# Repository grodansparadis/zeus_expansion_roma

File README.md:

<h1>Zeus Expansion Roma</h1>

433Mhz RF add on card with Zeus expansion connector. Fits the 
<a href="http://www.grodansparadis.com/odessa/odessa.html">Odessa</a> module
among other modules.

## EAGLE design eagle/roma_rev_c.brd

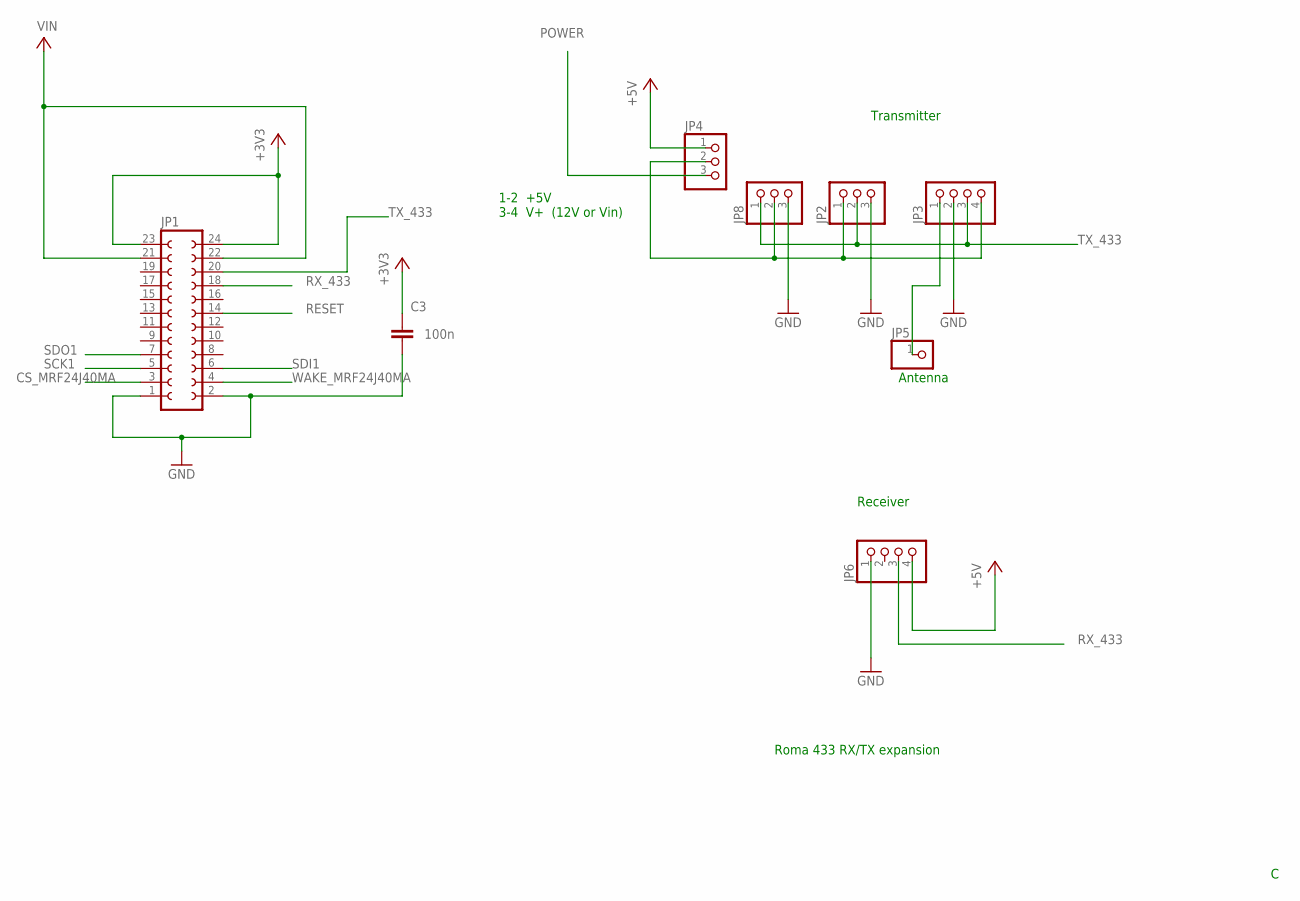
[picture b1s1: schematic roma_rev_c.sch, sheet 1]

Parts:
C3: 100n; C0805
JP1: FE12-2
JP2, JP4, JP8: PINHD-1X3; 1X03
JP3, JP6: PINHD-1X4; 1X04
JP5: PINHD-1X1; 1X01

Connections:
+3V3: C3.1, JP1.23, JP1.24; also elsewhere on the board
+5V: JP4.1, JP6.4; also elsewhere on the board
CS_MRF24J40MA: JP1.3; also elsewhere on the board
GND: C3.2, JP1.1, JP1.2, JP2.3, JP3.2, JP6.1, JP8.3; also elsewhere on the board
unnamed: JP2.1, JP3.4, JP4.2, JP8.2
unnamed: JP3.1, JP5.1
POWER: JP4.3; also elsewhere on the board
RESET: JP1.14; also elsewhere on the board
RX_433: JP1.18, JP6.3; also elsewhere on the board
SCK1: JP1.5; also elsewhere on the board
SDI1: JP1.6; also elsewhere on the board
SDO1: JP1.7; also elsewhere on the board
TX_433: JP1.20, JP2.2, JP3.3, JP8.1
VIN: JP1.21, JP1.22; also elsewhere on the board
WAKE_MRF24J40MA: JP1.4; also elsewhere on the board

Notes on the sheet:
Roma 433 RX/TX expansion
Transmitter
Antenna
Receiver
1-2 +5V 3-4 V+ (12V or Vin)

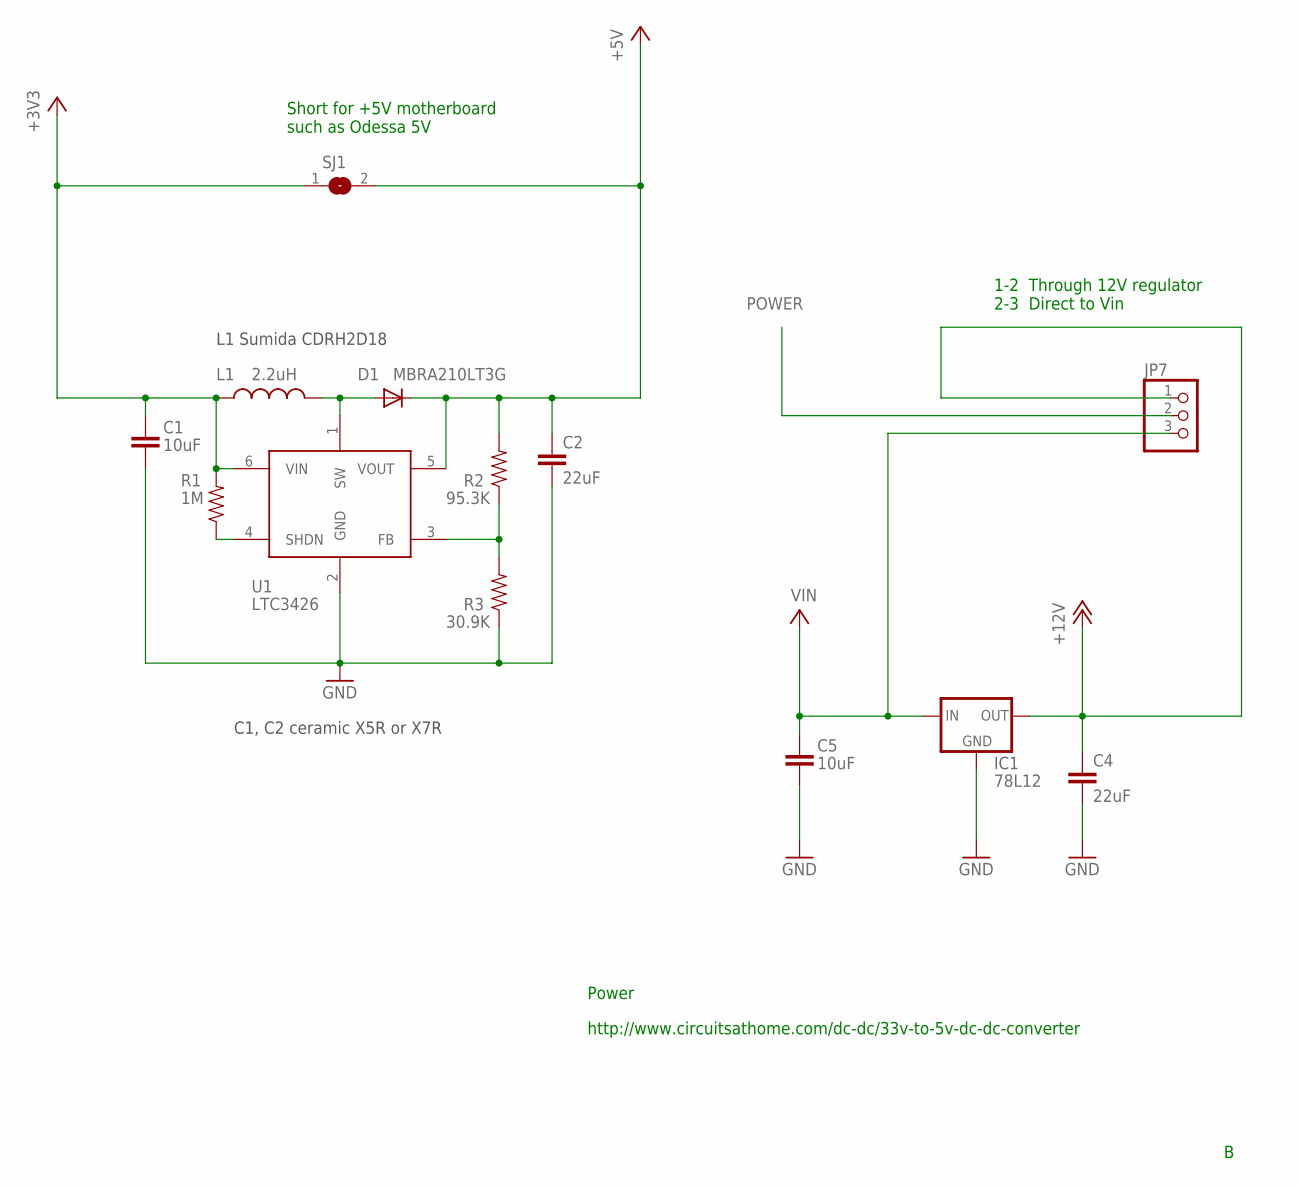
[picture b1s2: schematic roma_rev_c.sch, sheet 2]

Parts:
C1, C5: 10uF; 1210
C2, C4: 22uF; 1210
D1: MBRA210LT3G; SMA-DIODE
IC1: 78L12; 78LXX
JP7: PINHD-1X3; 1X03
L1: 2.2uH; 1_3X1_3
R1: 1M; 0805
R2: 95.3K; 0805
R3: 30.9K; 0805
SJ1: SJ
U1: LTC3426; SOT23-6

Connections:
+3V3: C1.1, L1.P$1 (1), R1.2, SJ1.1, U1.6 (VIN); also elsewhere on the board
+5V: C2.1, D1.C, R2.2, SJ1.2, U1.5 (VOUT); also elsewhere on the board
+12V: C4.1, IC1.OUT, JP7.1
GND: C1.2, C2.2, C4.2, C5.2, IC1.GND, R3.1, U1.2 (GND); also elsewhere on the board
unnamed: D1.A, L1.P$2 (2), U1.1 (SW)
unnamed: R1.1, U1.4 (SHDN)
unnamed: R2.1, R3.2, U1.3 (FB)
POWER: JP7.2; also elsewhere on the board
VIN: C5.1, IC1.IN, JP7.3; also elsewhere on the board

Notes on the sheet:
L1 Sumida CDRH2D18
C1, C2 ceramic X5R or X7R
http://www.circuitsathome.com/dc-dc/33v-to-5v-dc-dc-converter
Power
1-2 Through 12V regulator 2-3 Direct to Vin
Short for +5V motherboard such as Odessa 5V

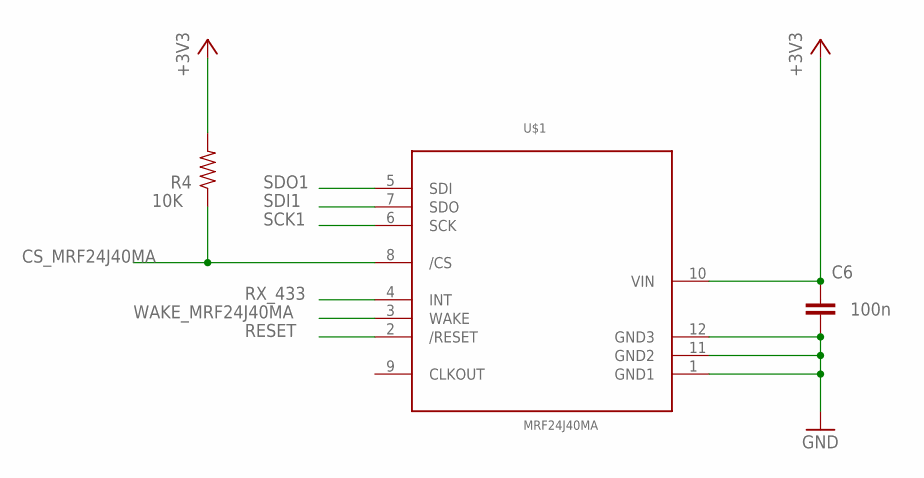
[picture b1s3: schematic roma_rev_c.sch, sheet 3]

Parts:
C6: 100n; C0805
R4: 10K; 0805
U$1: MRF24J40MA

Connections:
+3V3: C6.1, R4.2, U$1.10 (VIN); also elsewhere on the board
CS_MRF24J40MA: R4.1, U$1.8 (/CS); also elsewhere on the board
GND: C6.2, U$1.1 (GND1), U$1.11 (GND2), U$1.12 (GND3); also elsewhere on the board
RESET: U$1.2 (/RESET); also elsewhere on the board
RX_433: U$1.4 (INT); also elsewhere on the board
SCK1: U$1.6 (SCK); also elsewhere on the board
SDI1: U$1.7 (SDO); also elsewhere on the board
SDO1: U$1.5 (SDI); also elsewhere on the board
WAKE_MRF24J40MA: U$1.3 (WAKE); also elsewhere on the board

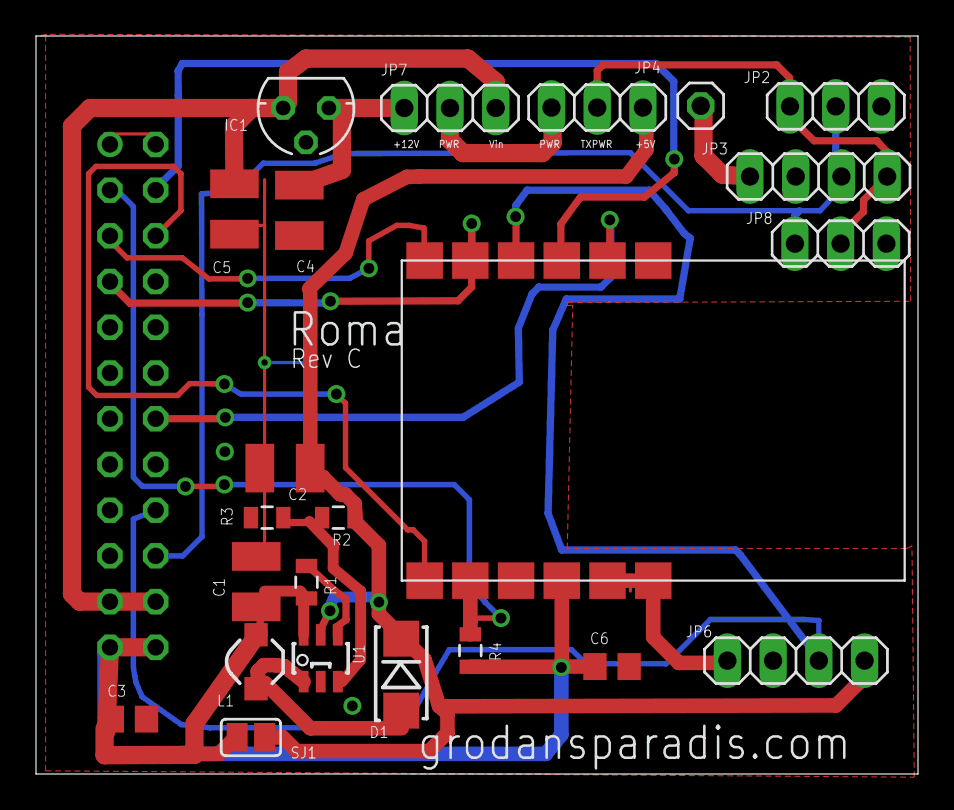
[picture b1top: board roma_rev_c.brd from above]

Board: 2 copper layers, 49.0 x 41.0 mm, 24 parts (1 on the bottom side), 19 nets.

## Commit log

2015-11-03 Making design open
2015-11-03 Removed some junk
2015-11-18 Moving old stuff out
2015-11-18 Renamed schemas to be consistent
2015-11-18 Moved some old files
2015-12-30 Added new transmitter pinout
2015-12-30 JP4 should be numbered the other way around. Added descriptive text.
2015-12-30 Added solder short to get +5V from Odessa 5V without converter.
2015-12-30 Redrawn signal that goes over transceiver protected zone
